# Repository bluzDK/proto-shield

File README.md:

Bluz Proto Shield Hardware Files
==========
Bluz is a Development Kit (DK) that implements the Wiring language and talks to the [Particle](https://www.particle.io/) cloud through Bluetooth Low Energy. It can be accessed through a REST API and programmed from a Web IDE.

These files have been made available online through a [Creative Commons Attribution-ShareAlike 3.0](http://creativecommons.org/licenses/by-sa/3.0/) license.

You are welcome to distribute, remix, and use these files for commercial purposes. If you do so, please attribute the original design to Bluz both on the website and on the physical packaging of the product or in the instruction manual. All derivative works must be published under the same or a similar license.

All items are subject to change over time as the product is designed, so make sure you are always looking at the latest information by pulling often.

##Sections
<b>BOM</b>: Current Bill of Materials for the proto shield.

<b>Datasheets</b>: Datasheets for all major parts on the board.

<b>HW Design</b>: Schematics, board layouts, and other design files.

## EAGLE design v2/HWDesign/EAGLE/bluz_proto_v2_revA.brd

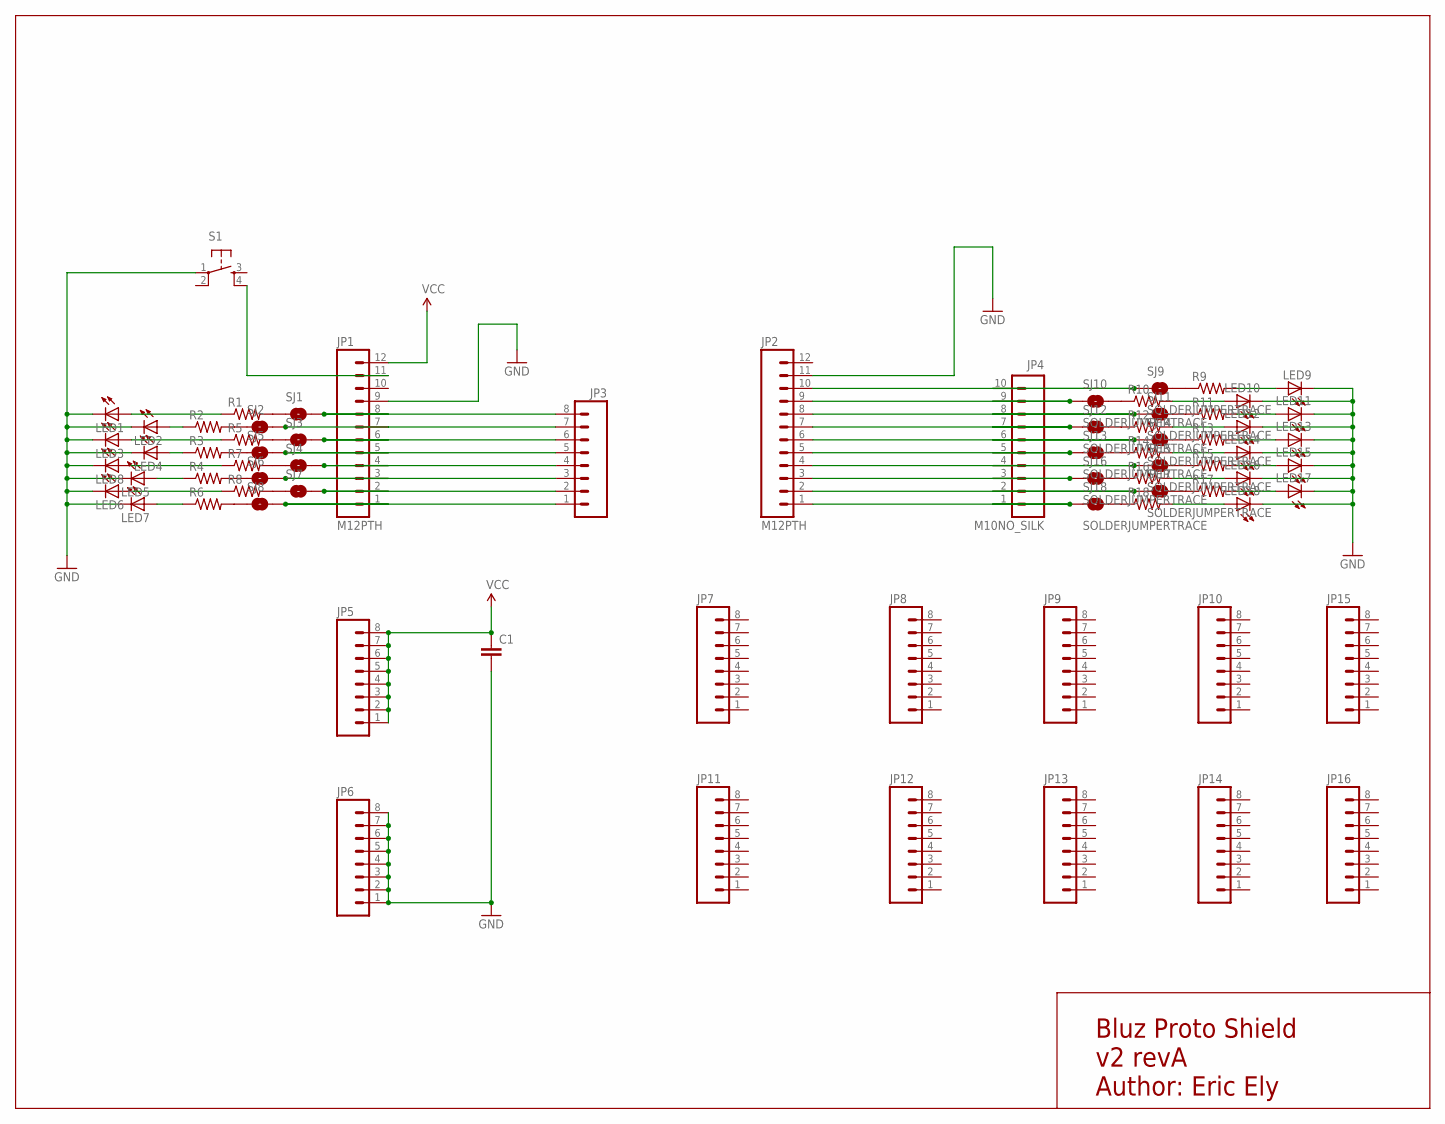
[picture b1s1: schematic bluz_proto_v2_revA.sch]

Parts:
C1: CAP0603-CAP; 0603-CAP
JP1, JP2: M12PTH; 1X12
JP3, JP5, JP6, JP7, JP8, JP9, JP10, JP11, JP12, JP13, JP14, JP15, JP16: M08NO_SILK; 1X08_NO_SILK
JP4: M10NO_SILK; 1X10_NO_SILK
LED1, LED2, LED3, LED4, LED5, LED6, LED7, LED8, LED9, LED10, LED11, LED12, LED13, LED14, LED15, LED16, LED17, LED18: LEDCHIP-LED0603; CHIP-LED0603
R1, R2, R3, R4, R5, R6, R7, R8, R9, R10, R11, R12, R13, R14, R15, R16, R17, R18: RESISTOR0603-RES; 0603-RES
S1: TAC_SWITCHSMD; TACTILE_SWITCH_SMD
SJ1, SJ2, SJ3, SJ4, SJ5, SJ6, SJ7, SJ8, SJ9, SJ10, SJ11, SJ12, SJ13, SJ14, SJ15, SJ16, SJ17, SJ18: SOLDERJUMPERTRACE; SJ_2S-TRACE

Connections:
GND: C1.2, JP1.9, JP2.11, JP6.1, JP6.2, JP6.3, JP6.4, JP6.5, JP6.6, JP6.7, JP6.8, LED1.C, LED2.C, LED3.C, LED4.C, LED5.C, LED6.C, LED7.C, LED8.C, LED9.C, LED10.C, LED11.C, LED12.C, LED13.C, LED14.C, LED15.C, LED16.C, LED17.C, LED18.C, S1.1
unnamed: JP1.1, JP3.1, SJ8.2
unnamed: JP1.2, JP3.2, SJ7.2
unnamed: JP1.3, JP3.3, SJ6.2
unnamed: JP1.4, JP3.4, SJ4.2
unnamed: JP1.5, JP3.5, SJ5.2
unnamed: JP1.6, JP3.6, SJ3.2
unnamed: JP1.7, JP3.7, SJ2.2
unnamed: JP1.8, JP3.8, SJ1.2
unnamed: JP2.1, JP4.1, SJ18.1
unnamed: JP2.2, JP4.2, SJ17.1
unnamed: JP2.3, JP4.3, SJ16.1
unnamed: JP2.4, JP4.4, SJ15.1
unnamed: JP2.5, JP4.5, SJ13.1
unnamed: JP2.6, JP4.6, SJ14.1
unnamed: JP2.7, JP4.7, SJ12.1
unnamed: JP2.8, JP4.8, SJ11.1
unnamed: JP2.9, JP4.9, SJ10.1
unnamed: JP2.10, JP4.10, SJ9.1
unnamed: LED6.A, R8.1
unnamed: R1.2, SJ1.1
unnamed: R2.2, SJ2.1
unnamed: R3.2, SJ5.1
unnamed: R4.2, SJ6.1
unnamed: R6.2, SJ8.1
unnamed: R5.2, SJ3.1
unnamed: R7.2, SJ4.1
unnamed: R8.2, SJ7.1
unnamed: LED1.A, R1.1
unnamed: LED2.A, R2.1
unnamed: LED3.A, R5.1
unnamed: LED4.A, R3.1
unnamed: LED5.A, R4.1
unnamed: LED7.A, R6.1
unnamed: LED8.A, R7.1
unnamed: R18.1, SJ18.2
unnamed: R17.1, SJ17.2
unnamed: R16.1, SJ16.2
unnamed: R15.1, SJ15.2
unnamed: R14.1, SJ13.2
unnamed: R13.1, SJ14.2
unnamed: R12.1, SJ12.2
unnamed: R11.1, SJ11.2
unnamed: R10.1, SJ10.2
unnamed: R9.1, SJ9.2
unnamed: LED9.A, R9.2
unnamed: LED10.A, R10.2
unnamed: LED11.A, R11.2
unnamed: LED12.A, R12.2
unnamed: LED13.A, R13.2
unnamed: LED14.A, R14.2
unnamed: LED15.A, R15.2
unnamed: LED16.A, R16.2
unnamed: LED17.A, R17.2
unnamed: LED18.A, R18.2
unnamed: JP1.11, S1.4
VCC: C1.1, JP1.12, JP5.1, JP5.2, JP5.3, JP5.4, JP5.5, JP5.6, JP5.7, JP5.8

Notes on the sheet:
Bluz Proto Shield v2 revA Author: Eric Ely

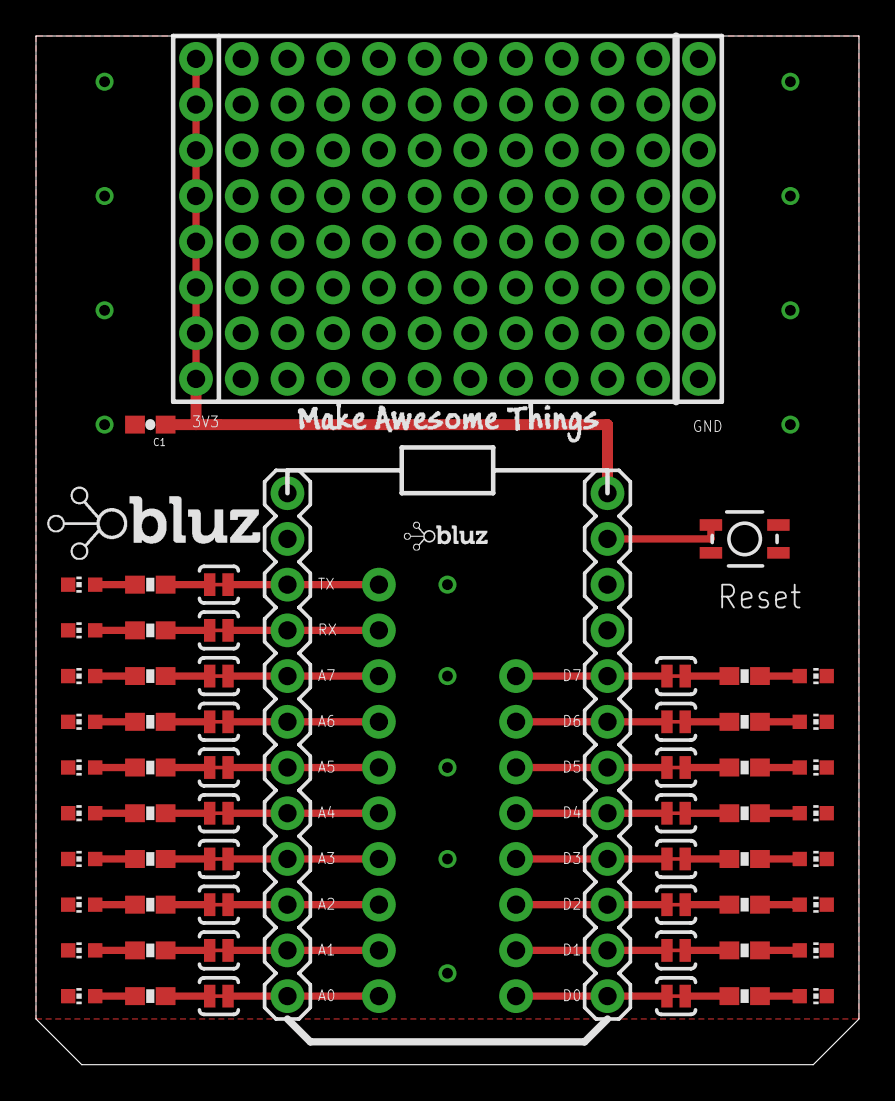
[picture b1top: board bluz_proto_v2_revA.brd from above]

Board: 2 copper layers, 45.7 x 57.1 mm, 75 parts (0 on the bottom side), 57 nets.

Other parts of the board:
U$2: BLUZ_LOGO_BETTER
U$3: BLUZE_LOGO_LOW_RES
U$4: MAKE_X2

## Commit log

2015-08-17 add more breakouts. add decoupling cap
2015-09-13 clarified wording in the BOM

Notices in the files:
parts and their libraries:
SparkFun-Connectors: Licensing: Creative Commons ShareAlike 4.0 International - https://creativecommons.org/licenses/by-sa/4.0
